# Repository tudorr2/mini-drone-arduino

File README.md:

# Mini Arduino Drone

A small drone built with an Arduino Nano, 4 brushed motors, an MPU6050 and an NRF24L01 radio. Includes a custom controller with 2 joysticks and an OLED display.

**Status:** work in progress. The radio link and motor control work. IMU reading and stabilization are not done yet.

---

## Gallery

|                        PCB                        |                                IRL                                |                            3D view                            |
| :-----------------------------------------------: | :---------------------------------------------------------------: | :-----------------------------------------------------------: |
|  |  |  |

---

## Parts

### Drone

| Part                             |  Qty  |
| -------------------------------- | :---: |
| Arduino Nano                     |   1   |
| Coreless DC motor 7×17 mm, 3.7 V |   4   |
| DRV8833 motor driver module      |   2   |
| NRF24L01 radio module            |   1   |
| MPU6050 (GY-521)                 |   1   |
| 5 V fixed boost converter        |   1   |
| 1S LiPo battery, 3.7 V           |   1   |
| 3D-printed frame and propellers  | 1 set |

### Controller

| Part                      | Qty |
| ------------------------- | :-: |
| Arduino Nano              |  1  |
| Analog joystick           |  2  |
| SSD1306 OLED 128×64 (I2C) |  1  |
| NRF24L01 radio module     |  1  |
| 18650 cells               |  2  |

---

## Pinout (drone)

| Nano pin        | Connects to              |
| --------------- | ------------------------ |
| D6              | DRV1 AIN1 (motor 1, PWM) |
| D2              | DRV1 AIN2 (LOW)          |
| D3              | DRV1 BIN1 (motor 2, PWM) |
| D4              | DRV1 BIN2 (LOW)          |
| D5              | DRV2 AIN1 (motor 3, PWM) |
| A0              | DRV2 AIN2 (LOW)          |
| D9              | DRV2 BIN1 (motor 4, PWM) |
| A1              | DRV2 BIN2 (LOW)          |
| D7 / D8         | NRF CE / CSN             |
| D11 / D12 / D13 | NRF MOSI / MISO / SCK    |
| A4 / A5         | MPU6050 SDA / SCL        |
| 5V              | Boost output             |
| 3V3             | NRF VCC                  |

## The AIN2/BIN2 pins are held LOW so each motor only runs in one direction. DRV VM goes to the battery.

## Setup

1. Install the Arduino libraries `RF24`, `Adafruit GFX` and `Adafruit SSD1306`.
2. Upload `code/drone/` to the drone and `code/controller/` to the controller.

Remove the propellers for first tests.

---

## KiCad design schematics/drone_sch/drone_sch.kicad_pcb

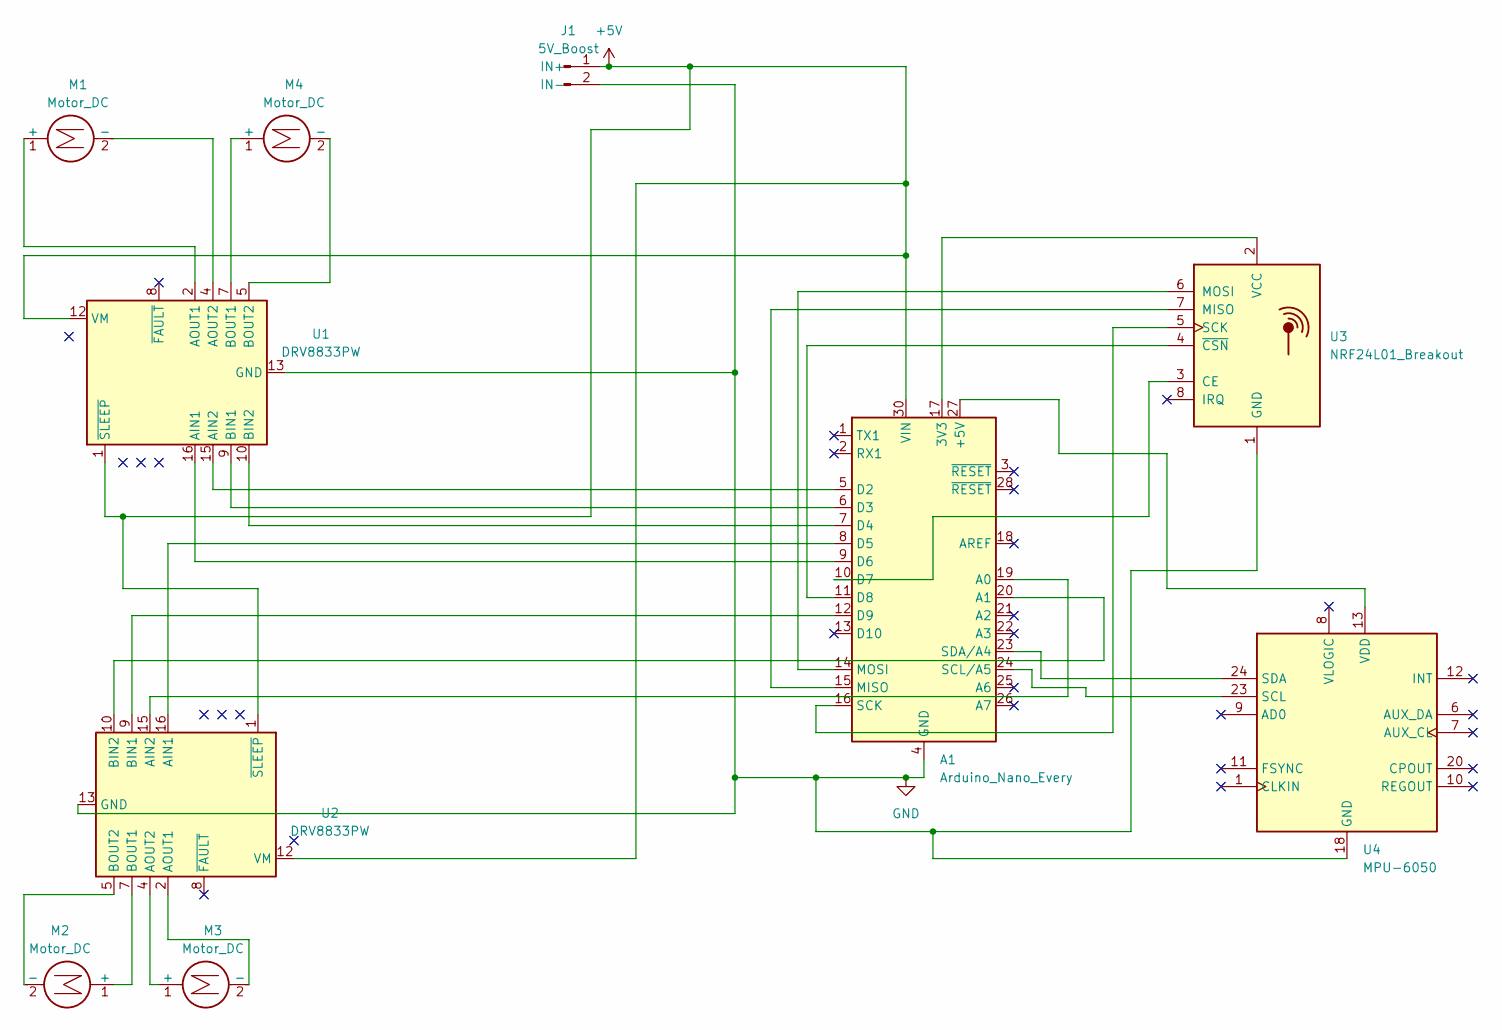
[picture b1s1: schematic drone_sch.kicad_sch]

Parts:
A1: Arduino_Nano_Every; Arduino_Nano
J1: 5V_Boost; TestPoint_2Pads_Pitch2.54mm_Drill0.8mm
M1, M2, M3, M4: Motor_DC; TestPoint_2Pads_Pitch2.54mm_Drill0.8mm
U1, U2: DRV8833PW; TSSOP-16_4.4x5mm_P0.65mm
U3: NRF24L01_Breakout; nRF24L01_Breakout
U4: MPU-6050; InvenSense_QFN-24_4x4mm_P0.5mm

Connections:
+5V: A1.30 (VIN), J1.1 (IN+), U1.1 (~SLEEP), U1.12 (VM), U2.1 (~SLEEP), U2.12 (VM)
GND: A1.4 (GND), A1.29 (GND), J1.2 (IN-), U1.13 (GND), U2.13 (GND), U3.1 (GND), U4.18 (GND)
unnamed: A1.17 (3V3), U3.2 (VCC)
unnamed: A1.27 (+5V), U4.13 (VDD)
unnamed: A1.19 (A0), U2.15 (AIN2)
unnamed: A1.20 (A1), U2.10 (BIN2)
unnamed: A1.5 (D2), U1.15 (AIN2)
unnamed: A1.6 (D3), U1.9 (BIN1)
unnamed: A1.7 (D4), U1.10 (BIN2)
unnamed: A1.8 (D5), U2.16 (AIN1)
unnamed: A1.9 (D6), U1.16 (AIN1)
unnamed: A1.10 (D7), U3.3 (CE)
unnamed: A1.11 (D8), U3.4 (~CSN)
unnamed: A1.12 (D9), U2.9 (BIN1)
unnamed: A1.15 (MISO), U3.7 (MISO)
unnamed: A1.14 (MOSI), U3.6 (MOSI)
unnamed: A1.16 (SCK), U3.5 (SCK)
unnamed: A1.24 (SCL/A5), U4.23 (SCL)
unnamed: A1.23 (SDA/A4), U4.24 (SDA)
unnamed: M1.1 (+), U1.2 (AOUT1)
unnamed: M1.2 (-), U1.4 (AOUT2)
unnamed: M2.1 (+), U2.7 (BOUT1)
unnamed: M2.2 (-), U2.5 (BOUT2)
unnamed: M3.1 (+), U2.4 (AOUT2)
unnamed: M3.2 (-), U2.2 (AOUT1)
unnamed: M4.1 (+), U1.7 (BOUT1)
unnamed: M4.2 (-), U1.5 (BOUT2)
VINT: U1.14 (VINT), U2.14 (VINT)

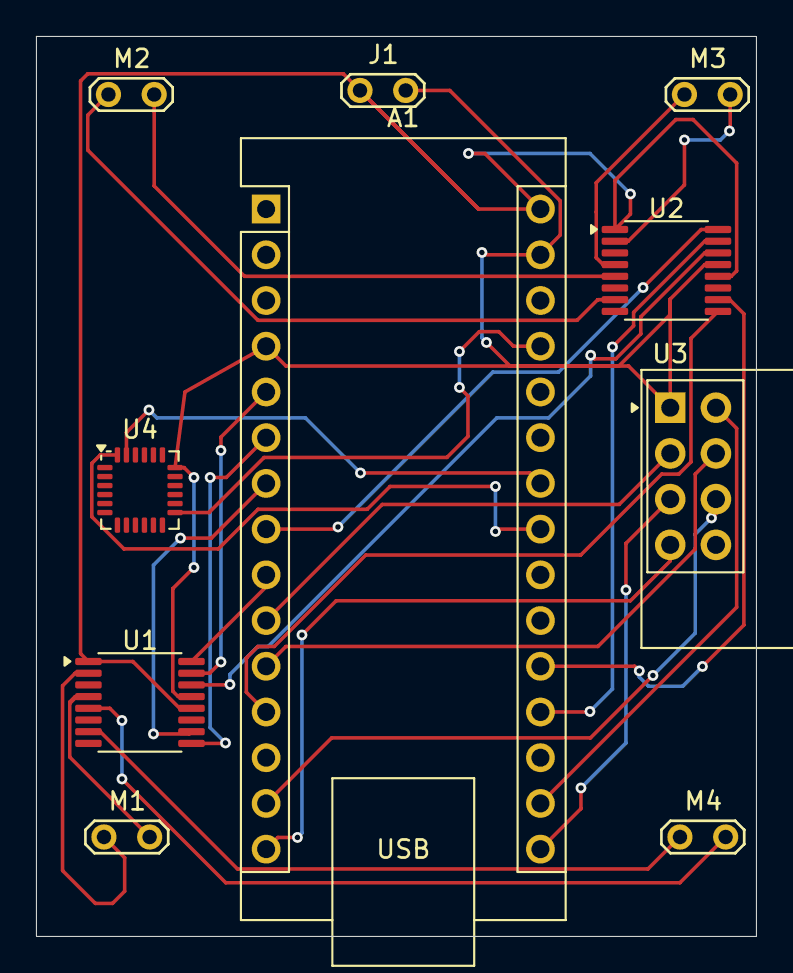
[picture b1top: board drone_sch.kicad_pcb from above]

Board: 2 copper layers, 40.0 x 50.0 mm, 10 parts (0 on the bottom side), 28 nets.
